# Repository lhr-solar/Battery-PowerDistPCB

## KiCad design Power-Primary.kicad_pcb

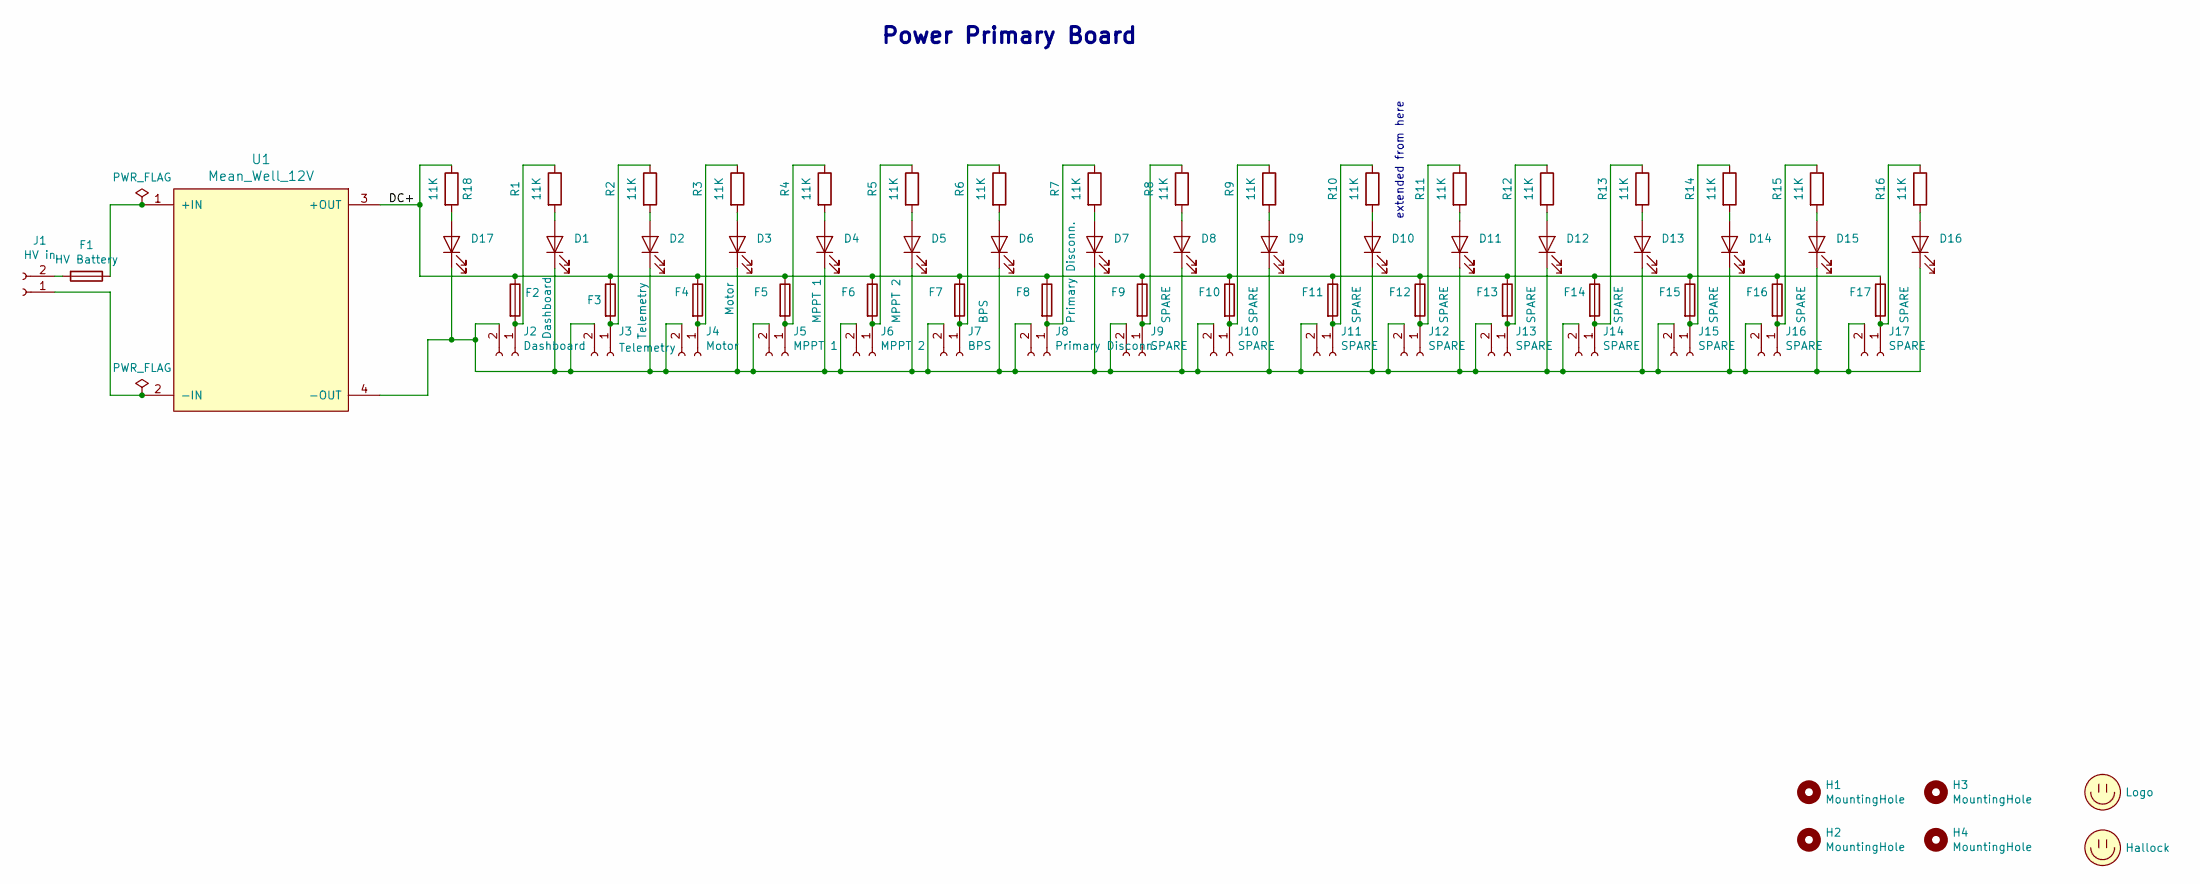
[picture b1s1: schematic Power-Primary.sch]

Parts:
D1, D2, D3, D4, D5, D6, D7, D8, D9, D10, D11, D12, D13, D14, D15, D16, D17: LED; LED_D3.0mm
F1: HV Battery; Fuseholder_Cylinder-5x20mm_Schurter_0031_8201_Horizontal_Op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
F2: Dashboard; Fuseholder_Blade_Mini_Keystone_3568
F3: Telemetry; Fuseholder_Blade_Mini_Keystone_3568
F4: Motor; Fuseholder_Blade_Mini_Keystone_3568
F5: MPPT 1; Fuseholder_Blade_Mini_Keystone_3568
F6: MPPT 2; Fuseholder_Blade_Mini_Keystone_3568
F7: BPS; Fuseholder_Blade_Mini_Keystone_3568
F8: Primary Disconn.; Fuseholder_Blade_Mini_Keystone_3568
F9, F10, F11, F12, F13, F14, F15, F16, F17: SPARE; Fuseholder_Blade_Mini_Keystone_3568
H1, H2, H3, H4: MountingHole; MountingHole_3mm
J1: HV in; PhoenixContact_PC_2-GF_2x7.62
J2: Dashboard; Molex_Micro-Fit_3.0_43650-0215_1x02_P3.00mm_Vertical
J3: Telemetry; Molex_Micro-Fit_3.0_43650-0215_1x02_P3.00mm_Vertical
J4: Motor; Molex_Micro-Fit_3.0_43650-0215_1x02_P3.00mm_Vertical
J5: MPPT 1; Molex_Micro-Fit_3.0_43650-0215_1x02_P3.00mm_Vertical
J6: MPPT 2; Molex_Micro-Fit_3.0_43650-0215_1x02_P3.00mm_Vertical
J7: BPS; Molex_Micro-Fit_3.0_43650-0215_1x02_P3.00mm_Vertical
J8: Primary Disconn.; Molex_Micro-Fit_3.0_43650-0215_1x02_P3.00mm_Vertical
J9, J10, J11, J12, J13, J14, J15, J16, J17: SPARE; Molex_Micro-Fit_3.0_43650-0215_1x02_P3.00mm_Vertical
LOGO1: Logo; UTSVT_Logo_Symbol
LOGO2: Hallock; Hallock_Image
R1, R2, R3, R4, R5, R6, R7, R8, R9, R10, R11, R12, R13, R14, R15, R16, R18: 11K; R_Axial_DIN0204_L3.6mm_D1.6mm_P7.62mm_Horizontal
U1: Mean_Well_12V; RSD-150

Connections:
/DC+: F2.1, F3.1, F4.1, F5.1, F6.1, F7.1, F8.1, F9.1, F10.1, F11.1, F12.1, F13.1, F14.1, F15.1, F16.1, F17.1, R18.1, U1.3 (+OUT)
unnamed: D1.1 (K), D2.1 (K), D3.1 (K), D4.1 (K), D5.1 (K), D6.1 (K), D7.1 (K), D8.1 (K), D9.1 (K), D10.1 (K), D11.1 (K), D12.1 (K), D13.1 (K), D14.1 (K), D15.1 (K), D16.1 (K), D17.1 (K), J2.2, J3.2, J4.2, J5.2, J6.2, J7.2, J8.2, J9.2, J10.2, J11.2, J12.2, J13.2, J14.2, J15.2, J16.2, J17.2, U1.4 (-OUT)
unnamed: D1.2 (A), R1.2
unnamed: D2.2 (A), R2.2
unnamed: D3.2 (A), R3.2
unnamed: D4.2 (A), R4.2
unnamed: D5.2 (A), R5.2
unnamed: D6.2 (A), R6.2
unnamed: D7.2 (A), R7.2
unnamed: D8.2 (A), R8.2
unnamed: D9.2 (A), R9.2
unnamed: D10.2 (A), R10.2
unnamed: D11.2 (A), R11.2
unnamed: D12.2 (A), R12.2
unnamed: D13.2 (A), R13.2
unnamed: D14.2 (A), R14.2
unnamed: D15.2 (A), R15.2
unnamed: D16.2 (A), R16.2
unnamed: D17.2 (A), R18.2
unnamed: F1.1, U1.1 (+IN)
unnamed: F1.2, J1.2
unnamed: F2.2, J2.1, R1.1
unnamed: F3.2, J3.1, R2.1
unnamed: F4.2, J4.1, R3.1
unnamed: F5.2, J5.1, R4.1
unnamed: F6.2, J6.1, R5.1
unnamed: F7.2, J7.1, R6.1
unnamed: F8.2, J8.1, R7.1
unnamed: F9.2, J9.1, R8.1
unnamed: F10.2, J10.1, R9.1
unnamed: F11.2, J11.1, R10.1
unnamed: F12.2, J12.1, R11.1
unnamed: F13.2, J13.1, R12.1
unnamed: F14.2, J14.1, R13.1
unnamed: F15.2, J15.1, R14.1
unnamed: F16.2, J16.1, R15.1
unnamed: F17.2, J17.1, R16.1
unnamed: J1.1, U1.2 (-IN)

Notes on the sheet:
extended from here
Power Primary Board

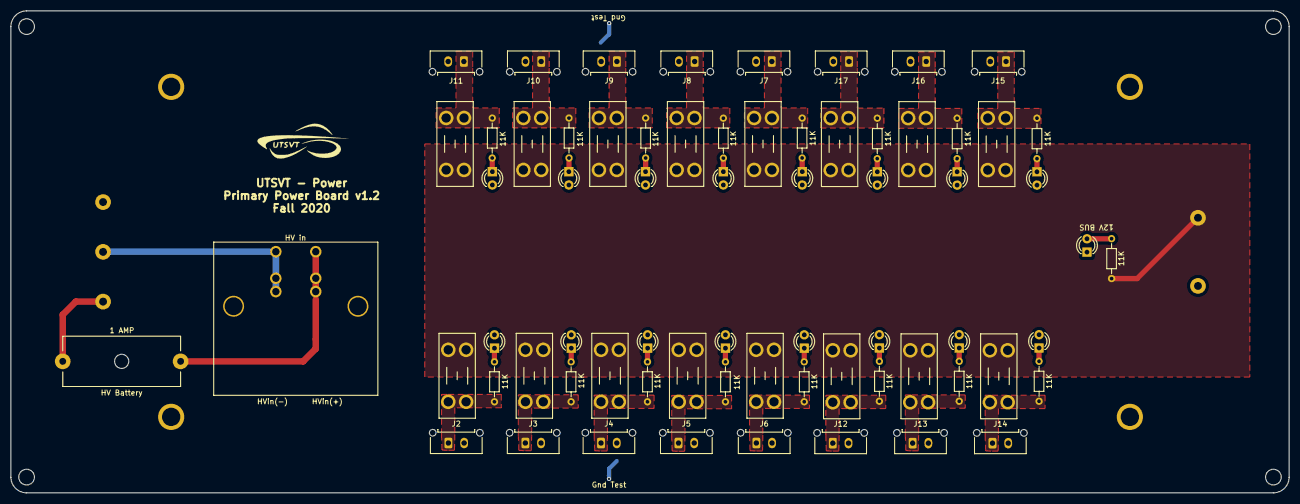
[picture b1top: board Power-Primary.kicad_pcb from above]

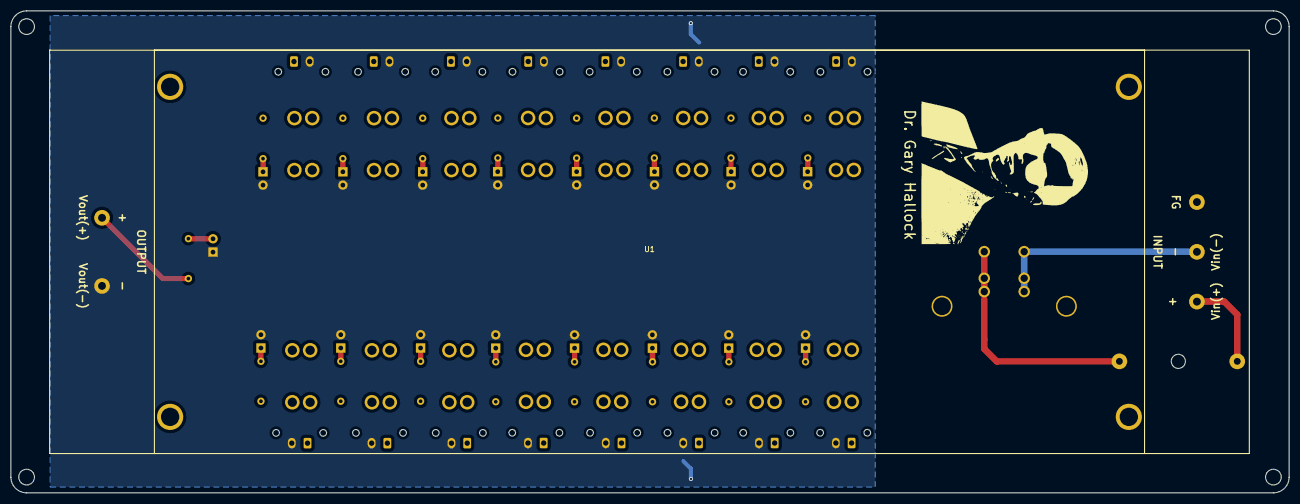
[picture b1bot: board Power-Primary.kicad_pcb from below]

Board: 2 copper layers, 244.0 x 92.0 mm, 75 parts (2 on the bottom side), 38 nets.

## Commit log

2020-08-02 Separate the power distribution board repository.
2020-09-01 Renames project name to Power-Primary and fixes library issues
2020-09-01 Adds UTSVT_Power footprint library
2020-09-07 Practice push + changed schematic
2020-09-08 schematic almost done, connection errors
2020-09-12 schematic done, U1 pin 3/4 error
2020-09-12 finished schematic
2020-09-27 finished PCB waiting for edits
2020-09-27 pcb edits
2020-09-29 fixed component spacing
2020-09-29 refilled zones
2020-10-01 Aligns half of the board to metric
2020-10-03 Adds QuAC
2020-10-03 completed Hannah's edits
2020-10-03 Sijin's edits, mounting hole and power planes
2020-10-03 Deletes gerbers from this because added to release and adds dimensions
2020-10-03 Extend design (#1)
    * Practice push + changed schematic
    * schematic almost done, connection errors
    * schematic done, U1 pin 3/4 error
    * finished schematic
    * finished PCB waiting for edits
    * pcb edits
2020-10-10 Add STEP files. Some connectors still missing
2020-10-17 Adds pdf and png documentation files of schematic and pcb
2020-11-28 Added mounting holes and updated pcb/sch
2021-01-11 Adds gerbers and gets rid of binding labels
2021-01-12 Changes DC DC Converter to one that has more power
2021-01-23 Edits to the common repo
2021-01-23 Adds 3D Model
2021-01-23 Adds 3D Model (#2)
2021-01-23 Adds stl of 3D model
2021-01-23 Pushes changes to common
2021-01-23 Updates common repo
2021-01-23 Adds stl file
